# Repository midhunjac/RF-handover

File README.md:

# RF-Wireless-Sensors

# Getting started with STM32

Download STM32CubeProgrammer and STM32CubeIDE. Also download the STM drivers for Windows.<br>
Use the FTDI cable to flash images.<br>
To flash the image, the MCU must be in bootloader mode. To put it in bootloader mode, connect FTDI cable according to the schematics as shown below.<br><br>
FTDI cable to board connections.<br>

Red         ----        Power<br>
Black       ----        Ground<br>
Yellow      ----        TX<br>
Orange      ----        RX<br>
Red         ----        Boot0<br>

Boot0 must be pulled high. Additionally, press down the RESET button while plugging in the FTDI cable. Once plugged in, release the RESET button. AT this point, the device is in bootloader mode and the MCU should not be advertising.
In the STM32CubeProgrammer, change connect mode to UART. Choose the new COM port from the dropdown. Keep everything else at default.If everything is set properly, the programmer should be able to connect to the device properly.
On the left-hand menu, go to 'Erasing and Programming' section. Customize the options as needed. Set the start address as 0x8000000. Choose the binary file from browser. Start programming. The new file should be transferred and the device will be disconnected. Disconnect the BOOT0 pin from power and power the device.

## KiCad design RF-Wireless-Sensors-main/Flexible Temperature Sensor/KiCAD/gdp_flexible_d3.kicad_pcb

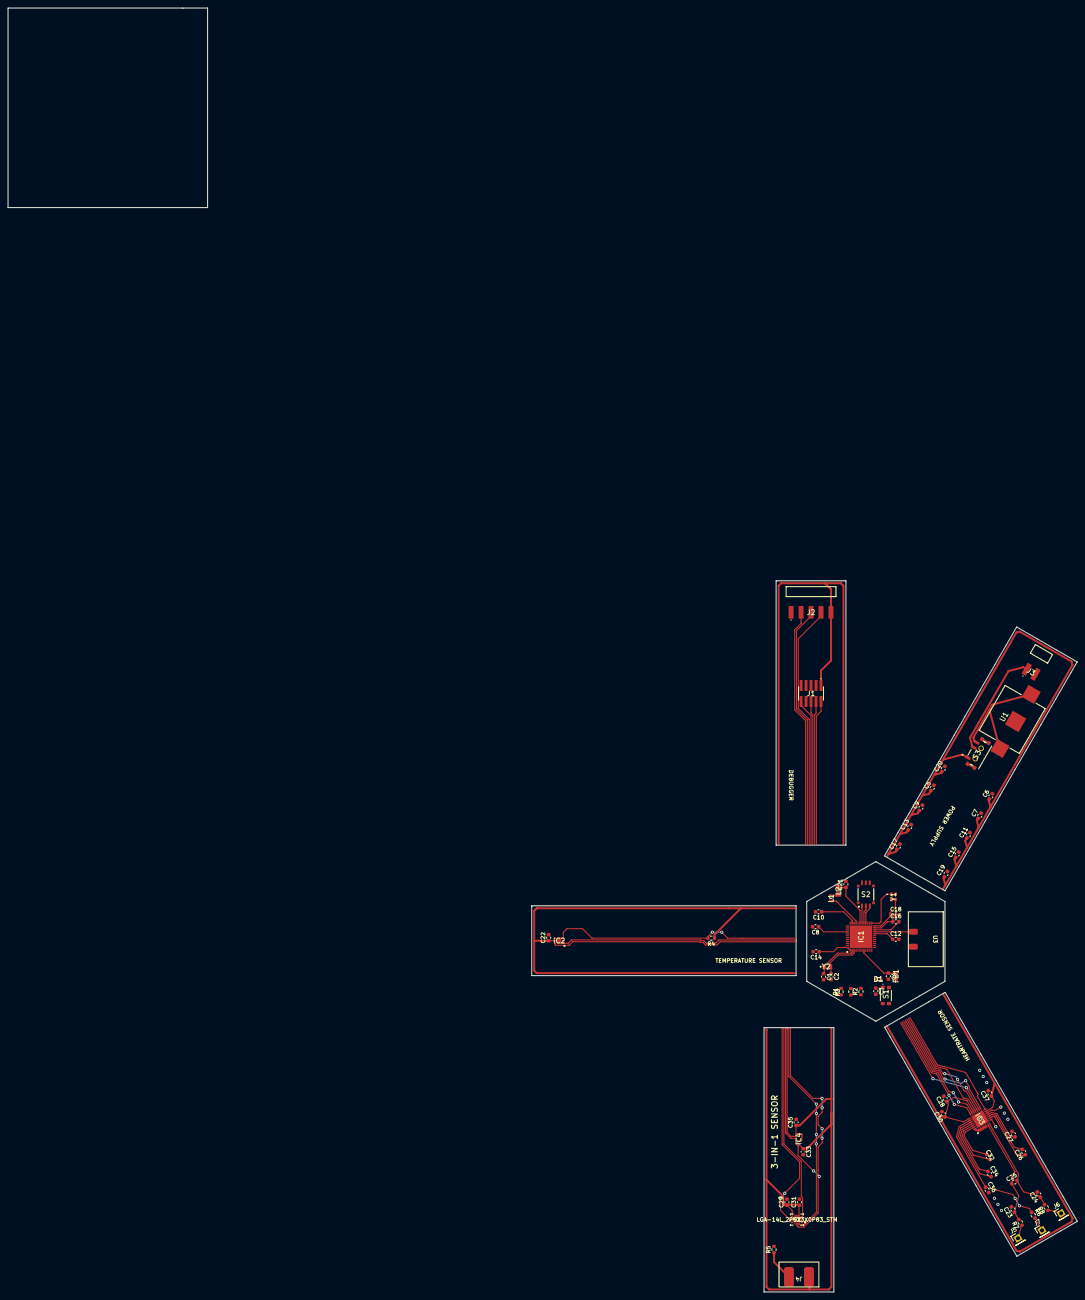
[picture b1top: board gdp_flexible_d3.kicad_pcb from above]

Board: 2 copper layers, 272.3 x 326.9 mm, 68 parts (0 on the bottom side), 50 nets.

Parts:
C1, C2, C3, C4, C5, C6, C7, C8, C9, C10, C11, C12, C13, C14, C15, C16, C17, C18, C19, C20, C21, C22, C23, C24, C25, C26, C27, C28, C29, C30, C31, C32, C33, C34, C35, C36, C37: C; C_0603_1608Metric
D1: BAT54KFILM; SODFL1608X70N
FB1: HZ0603C601R-10; BEADC1608X95N
IC1: STM32WB15CCU6; QFN50P700X700X60-49N-D
IC2: TMP117MAIDRVR; SON65P200X200X80-7N
IC3: MAX30003CTI+; QFN50P500X500X80-29N
IC4: LIS2DW12TR; LGA-12
J1: FTS-105-01-F-DV-TR; FTS-105-YY-XX-DV-TR
J2: TSM-105-01-T-SH; TSM-105-YY-ZZZ-SH
J3: TSM-102-01-L-SH; TSM-102-YY-ZZZ-SH
J4: FSR07CE
J5, J6, J7: Conn_01x01; PinHeader_1x01_P2.54mm_Vertical
L1: LQW18AN10NG00D; LQW18AS10NG0CD
L2: 74479777310A; INDC2112X140N
R1, R2, R3, R4, R5, R6, R7, R8: R; R_0603_1608Metric
S1: KMR231GLFS; KMR2_1
S2: CVS-03TB; CVS03TB
S3: CUS-12TB; CUS-12B
U1: S8201-46R
U2: LGA-14L_2P5X3X0P83_STM; LSM6DSMTR
U3: Antenna_Flexible_BLE
Y1: NX2016SA-32MHZ-EXS00A-CS06654; NX2016SA32MHZEXS00ACS06654
Y2: NX2012SA-32.768KHZ-EXS00A-MU00389; NX2012SA32768KHZEXS00AMU00530

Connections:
/CADENCE_INT1: IC1.47 (PB7), IC4.11 (INT2)
/CADENCE_INT2: IC1.46 (PB6), IC4.12 (INT1)
/CAPN: C26.2, IC3.10 (CAPN)
/CAPP: C26.1, IC3.9 (CAPP)
/COMP1_INP: IC1.19 (PB2), J4.2, R5.1
/CPPL: C27.1, IC3.11 (CPLL)
/ECGN: C24.1, C25.2, IC3.7 (ECGN), R8.2
/ECG_P: C23.1, C25.1, IC3.6 (ECGP), R7.2
/HANDPOS_INT1: IC1.45 (PB5), U2.4 (INT1)
/HANDPOS_INT2: IC1.44 (PB4), U2.9 (INT2)
/HR_INT1: IC1.11 (PA2), IC3.21 (INTB)
/HR_INT2: IC1.12 (PA3), IC3.20 (INT2B)
/I2C1_SCL: IC1.5 (PB8), IC2.1 (SCL), IC4.1 (SCL/SPC), R3.2, U2.13 (SCL)
/I2C1_SDA: IC1.6 (PB9), IC2.6 (SDA), IC4.4 (SDA/SDI/SDO), R2.2, U2.14 (SDA)
/MODE_B1: IC1.30 (PE4), S2.A1 (COM_1)
/MODE_B2: IC1.29 (PB1), S2.A2 (COM_2)
/MODE_B3: IC1.28 (PB0), S2.A3 (COM_3)
/NRST: D1.1, J1.10, S1.1, S1.3
/OSC_IN: IC1.25 (OSC_IN), Y1.1 (CRYSTAL_1)
/OSC_OUT: IC1.24 (OSC_OUT), Y1.3 (CRYSTAL_2)
/PB11-NRST: C3.1, D1.2, IC1.7 (NRST)
/PC14-OSC32_IN: C1.1, IC1.2 (PC14-OSC32_IN), Y2.1
/PC15-OSC32_OUT: C2.1, IC1.3 (PC15-OSC32_OUT), Y2.2
/PH3-BOOT0: IC1.4 (PH3-BOOT0), J2.4, R1.2
/RCC_MCO: IC1.17 (PA8), IC3.14 (FCLK)
/RF1: IC1.21 (RF1), U3.1
/SPI1_MISO: IC1.15 (PA6), IC3.18 (SDO)
/SPI1_MOSI: IC1.14 (PA5), IC3.17 (SDI)
/SPI1_NSS: IC1.13 (PA4), IC3.15 (CSB)
/SPI1_SCK: IC1.10 (PA1), IC3.16 (SCLK)
/SYS_JTCK-SWCLK: IC1.41 (PA14), J1.4
/SYS_JTDO-SWO: IC1.43 (PB3), J1.6
/SYS_JTMS-SWDIO: IC1.39 (PA13), J1.2
/TEMP_INT: IC1.42 (PA15), IC2.3 (ALERT), R4.2
/USART1_RX: IC1.36 (PA10), J2.3
/USART1_TX: IC1.18 (PA9), J2.2
/VBG: C32.1, IC3.27 (VBG)
/VCM: C34.1, IC3.25 (VCM)
/VDAA: C4.1, FB1.2, IC1.8 (VDDA)
/VDD_BAT: S3.3, U1.1, U1.3
/VDD_PS: J3.1, S3.2
/VFBSMPS: C21.1, IC1.31 (VFBSMPS), L2.2
/VLXSMPS: IC1.33 (VLXSMPS), L1.1
/VREF: C36.1, IC3.23 (VREF), R6.1
GND: C1.2, C2.2, C3.2, C4.2, C5.2, C6.2, C7.2, C8.2, C9.2, C10.2, C11.2, C12.2, C13.2, C14.2, C15.2, C16.2, C17.2, C18.2, C19.2, C20.2, C21.2, C22.2, C23.2, C24.2, C27.2, C28.2, C29.2, C30.2, C31.2, C32.2, C33.2, C34.2, C35.2, C36.2, C37.2, IC1.22 (VSSRF), IC1.32 (VSSSMPS), IC1.49 (EP), IC2.2 (GND), IC2.4 (ADD0), IC3.1 (I.C._1), IC3.2 (I.C._2), IC3.3 (AGND_1), IC3.4 (I.C._3), IC3.5 (I.C._4), IC3.8 (AGND_2), IC3.12 (DGND), IC3.24 (I.C._5), IC3.26 (I.C._6), IC3.28 (AGND_3), IC3.29 (THERMAL_PAD), IC4.6 (GND_1), IC4.7 (RES), IC4.8 (GND_2), J1.3, J1.5, J2.1, J3.2, R1.1, R5.2, S1.2, S1.4, S2.MP1, S2.MP2, S2.MP3, S2.MP4, S3.4, S3.5, S3.6, S3.7, U1.2, U2.1 (SDO/SA0), U2.2 (SDx), U2.3 (SCx), U2.6 (GND), U2.7 (GND), U3.2, Y1.2 (GND_1), Y1.4 (GND_2)
unnamed: J5.1, R7.1
unnamed: J6.1, R8.1
unnamed: J7.1, R6.2
unnamed: L1.2, L2.1
VDD: C5.1, C6.1, C7.1, C8.1, C9.1, C10.1, C11.1, C12.1, C13.1, C14.1, C15.1, C16.1, C17.1, C18.1, C19.1, C20.1, C22.1, C28.1, C29.1, C30.1, C31.1, C33.1, C35.1, C37.1, FB1.1, IC1.1 (VBAT), IC1.20 (VDD_1), IC1.23 (VDDRF), IC1.34 (VDDSMPS), IC1.35 (VDD_2), IC1.40 (VDD_3), IC1.48 (VDD_4), IC2.5 (V+), IC3.13 (DVDD), IC3.19 (OVDD), IC3.22 (AVDD), IC4.2 (CS), IC4.9 (VDD), IC4.10 (VDDIO), J1.1, J2.5, J4.1, R2.1, R3.1, R4.1, S2.B1 (NO_1), S2.B2 (NO_2), S2.B3 (NO_3), S3.1, U2.5 (VDDIO), U2.8 (VDD)

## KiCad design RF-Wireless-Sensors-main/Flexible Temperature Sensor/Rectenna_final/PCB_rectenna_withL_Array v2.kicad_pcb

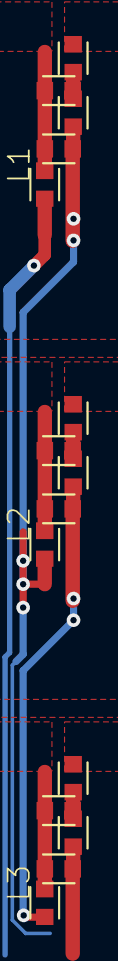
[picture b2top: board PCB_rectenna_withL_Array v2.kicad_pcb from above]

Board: 2 copper layers, 15 parts (0 on the bottom side), 9 nets.

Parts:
C1, C2, C3, C4, C5, C6, C7, C8, C9, C10, C11, C12: CAPC1608X85
L1, L2, L3: INDC1608X95N

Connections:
ADC: C6.1, C7.1, L2.1
ANTIN: C4.1, C5.1, C7.2, L1.2
ANTIN2: C1.1, C2.1, C8.2, L2.2
ANTIN4: C9.1, C10.1, C12.2, L3.2
INPUT1: C3.1, C8.1, L3.1
INPUT2: C11.1, C12.1
unnamed: C1.2, C2.2, C3.2
unnamed: C9.2, C10.2, C11.2
unnamed: C4.2, C5.2, C6.2

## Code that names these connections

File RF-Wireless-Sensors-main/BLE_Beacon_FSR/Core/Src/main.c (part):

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  __HAL_RCC_GPIOA_CLK_ENABLE();
  __HAL_RCC_GPIOE_CLK_ENABLE();

  /*Configure GPIO pin : PH3 */
  GPIO_InitStruct.Pin = GPIO_PIN_3;
  GPIO_InitStruct.Mode = GPIO_MODE_ANALOG;
  GPIO_InitStruct.Pull = GPIO_NOPULL;
  HAL_GPIO_Init(GPIOH, &GPIO_InitStruct);

  /*Configure GPIO pins : PB8 PB9 PB0 PB1
                           PB3 PB4 PB5 PB6
                           PB7 */
  GPIO_InitStruct.Pin = GPIO_PIN_8|GPIO_PIN_9|GPIO_PIN_0|GPIO_PIN_1
                          |GPIO_PIN_3|GPIO_PIN_4|GPIO_PIN_5|GPIO_PIN_6
                          |GPIO_PIN_7;
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  GPIO_InitStruct.Pull = GPIO_NOPULL;
  HAL_GPIO_Init(GPIOB, &GPIO_InitStruct);

  /*Configure GPIO pins : PA0 PA1 PA2 PA3
                           PA4 PA5 PA6 PA7
                           PA8 PA9 PA10 PA11
                           PA12 PA13 PA14 PA15 */
  GPIO_InitStruct.Pin = GPIO_PIN_0|GPIO_PIN_1|GPIO_PIN_2|GPIO_PIN_3
                          |GPIO_PIN_4|GPIO_PIN_5|GPIO_PIN_6|GPIO_PIN_7
                          |GPIO_PIN_8|GPIO_PIN_9|GPIO_PIN_10|GPIO_PIN_11
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  GPIO_InitStruct.Pull = GPIO_NOPULL;
  HAL_GPIO_Init(GPIOA, &GPIO_InitStruct);

  /*Configure GPIO pin : PE4 */
  GPIO_InitStruct.Pin = GPIO_PIN_4;
  GPIO_InitStruct.Mode = GPIO_MODE_ANALOG;
  GPIO_InitStruct.Pull = GPIO_NOPULL;
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
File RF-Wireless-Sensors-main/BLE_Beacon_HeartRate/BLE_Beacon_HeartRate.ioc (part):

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Mcu.Name=STM32WB15CCUx
Mcu.Package=UFQFPN48
Mcu.UserName=STM32WB15CCUx
PA1.Mode=Full_Duplex_Master
PA1.Signal=SPI1_SCK
PA10.Mode=Asynchronous
PA10.Signal=USART1_RX
PA3.GPIOParameters=GPIO_ModeDefaultEXTI
PA3.GPIO_ModeDefaultEXTI=GPIO_MODE_IT_FALLING
PA3.Signal=GPXTI3
PA4.GPIOParameters=GPIO_Label
PA4.GPIO_Label=SPI1_CS
PA4.Signal=GPIO_Output
PA5.Mode=Full_Duplex_Master
PA5.Signal=SPI1_MOSI
PA6.Mode=Full_Duplex_Master
PA6.Signal=SPI1_MISO
PA8.Mode=Clock-out
PA8.Signal=RCC_MCO
PA9.Mode=Asynchronous
PA9.Signal=USART1_TX
PC14-OSC32_IN.Mode=LSE-External-Oscillator
PC14-OSC32_IN.Signal=RCC_OSC32_IN
PC15-OSC32_OUT.Mode=LSE-External-Oscillator
PC15-OSC32_OUT.Signal=RCC_OSC32_OUT
RCC.HSE_VALUE=32000000
RCC.SYSCLKFreq_VALUE=32000000
RCC.SYSCLKSource=RCC_SYSCLKSOURCE_HSE
board=custom

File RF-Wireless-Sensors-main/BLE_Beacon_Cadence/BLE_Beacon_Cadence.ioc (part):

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Mcu.Name=STM32WB15CCUx
Mcu.Package=UFQFPN48
Mcu.UserName=STM32WB15CCUx
PA10.Mode=Asynchronous
PA10.Signal=USART1_RX
PA9.Mode=Asynchronous
PA9.Signal=USART1_TX
PB6.Signal=GPXTI6
PB8.Mode=I2C
PB8.Signal=I2C1_SCL
PB9.Mode=I2C
PB9.Signal=I2C1_SDA
PC14-OSC32_IN.Mode=LSE-External-Oscillator
PC14-OSC32_IN.Signal=RCC_OSC32_IN
PC15-OSC32_OUT.Mode=LSE-External-Oscillator
PC15-OSC32_OUT.Signal=RCC_OSC32_OUT
RCC.HSE_VALUE=32000000
RCC.SYSCLKFreq_VALUE=32000000
RCC.SYSCLKSource=RCC_SYSCLKSOURCE_HSE
board=custom

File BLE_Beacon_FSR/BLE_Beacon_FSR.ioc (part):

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Mcu.Name=STM32WB15CCUx
Mcu.Package=UFQFPN48
Mcu.UserName=STM32WB15CCUx
PB2.Mode=INP
PB2.Signal=COMP1_INP
PC14-OSC32_IN.Mode=LSE-External-Oscillator
PC14-OSC32_IN.Signal=RCC_OSC32_IN
PC15-OSC32_OUT.Mode=LSE-External-Oscillator
PC15-OSC32_OUT.Signal=RCC_OSC32_OUT
RCC.HSE_VALUE=32000000
RCC.SYSCLKFreq_VALUE=32000000
RCC.SYSCLKSource=RCC_SYSCLKSOURCE_HSE
board=custom

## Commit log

2024-02-27 All the PCBs and code
2024-02-27 Adding UI for a receiver
2024-02-27 Adding Getting started with STM32 section
2024-02-27 Reverting to single temperature sensor

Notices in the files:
RF-Wireless-Sensors-main/BLE_Beacon_FSR/Core/Src/main.c:
Copyright (c) 2023 STMicroelectronics.
All rights reserved.
This software is licensed under terms that can be found in the LICENSE file
parts and their libraries:
Copyright 2021 Accelerated Designs. All rights reserved.
